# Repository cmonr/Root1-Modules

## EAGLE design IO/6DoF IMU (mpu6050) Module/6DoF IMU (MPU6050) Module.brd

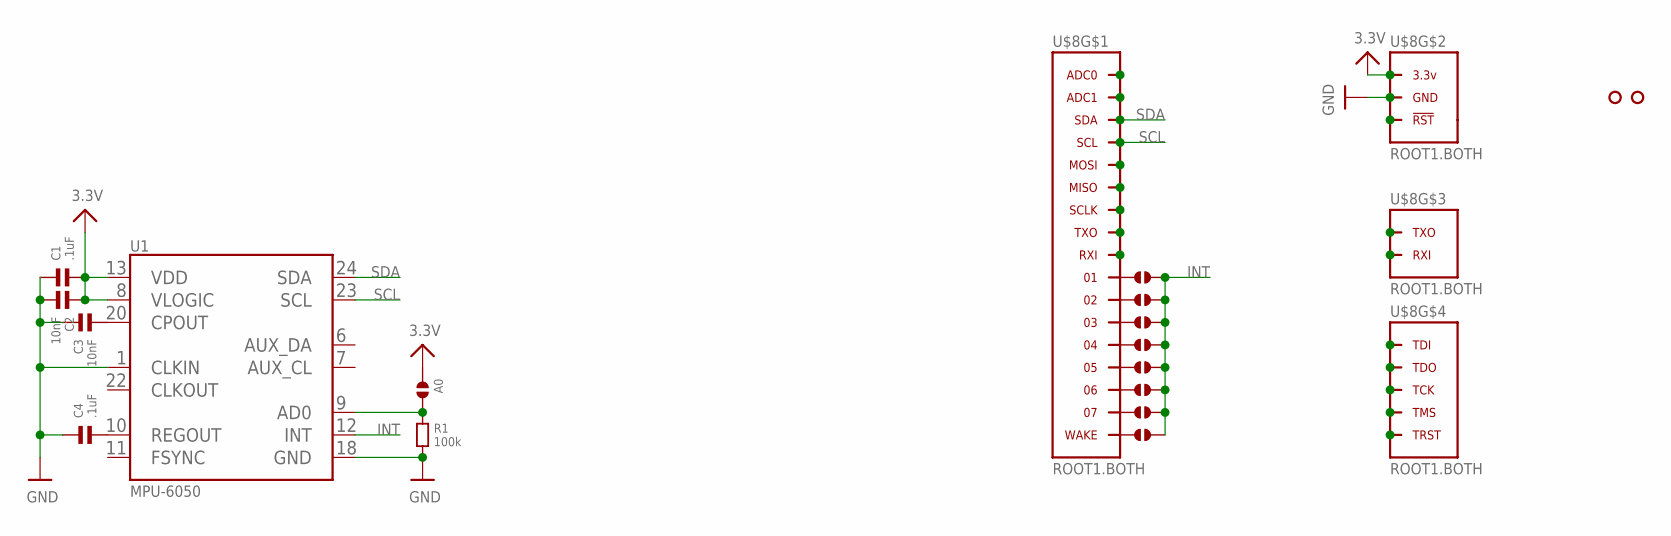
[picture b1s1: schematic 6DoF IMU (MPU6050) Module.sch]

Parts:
A0: SOLDERJUMPER.2.LRG; 2.LRG
C1, C4: .1uF; 0603
C2, C3: 10nF; 0603
J1, J2, J3, J4, J5, J6, J7, J8: SOLDERJUMPER.2.SML; 2.SML
R1: 100k; 0603
U1: MPU-6050; QFN
U$3, U$4: HOLE.2MM; 2MM
U$8: ROOT1.BOTH

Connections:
3.3V: A0.1, C1.2, C2.1, U1.8 (VLOGIC), U1.13 (VDD), U$8.3.3V@1 (3.3V), U$8.3.3V@2 (3.3V), U$8.3.3V@3 (3.3V), U$8.3.3V@4 (3.3V), U$8.3.3V@5 (3.3V), U$8.3.3V@6 (3.3V), U$8.3.3V@7 (3.3V), U$8.3.3V@8 (3.3V), U$8.3.3V@9 (3.3V), U$8.3.3V@10 (3.3V), U$8.3.3V@11 (3.3V), U$8.3.3V@12 (3.3V), U$8.3.3V@13 (3.3V), U$8.3.3V@14 (3.3V), U$8.3.3V@15 (3.3V), U$8.3.3V@16 (3.3V), U$8.3.3V@17 (3.3V), U$8.3.3V@18 (3.3V), U$8.3.3V@19 (3.3V), U$8.3.3V@20 (3.3V), U$8.3.3V@21 (3.3V), U$8.3.3V@22 (3.3V), U$8.3.3V@23 (3.3V), U$8.3.3V@24 (3.3V), U$8.3.3V@VIA (3.3V)
GND: C1.1, C2.2, C3.1, C4.1, R1.2, U1.1 (CLKIN), U1.18 (GND), U$8.GND@1 (GND), U$8.GND@2 (GND), U$8.GND@3 (GND), U$8.GND@4 (GND), U$8.GND@5 (GND), U$8.GND@6 (GND), U$8.GND@7 (GND), U$8.GND@8 (GND), U$8.GND@9 (GND), U$8.GND@10 (GND), U$8.GND@11 (GND), U$8.GND@12 (GND), U$8.GND@13 (GND), U$8.GND@14 (GND), U$8.GND@15 (GND), U$8.GND@16 (GND), U$8.GND@17 (GND), U$8.GND@18 (GND), U$8.GND@19 (GND), U$8.GND@20 (GND), U$8.GND@21 (GND), U$8.GND@22 (GND), U$8.GND@23 (GND), U$8.GND@24 (GND), U$8.GND@25 (GND), U$8.GND@26 (GND), U$8.GND@VIA (GND)
INT: J1.2, J2.2, J3.2, J4.2, J5.2, J6.2, J7.2, J8.2, U1.12 (INT)
unnamed: U$8.ADC0, U$8.ADC0@1 (ADC0), U$8.ADC0@VIA (ADC0)
unnamed: U$8.ADC1, U$8.ADC1@1 (ADC1), U$8.ADC1@VIA (ADC1)
unnamed: J1.1, U$8.01, U$8.01@1 (01), U$8.01@VIA (01)
unnamed: U$8.RST (!RST), U$8.RST@1 (!RST), U$8.RST@VIA (!RST)
unnamed: U$8.MOSI, U$8.MOSI@1 (MOSI), U$8.MOSI@VIA (MOSI)
unnamed: U$8.MISO, U$8.MISO@1 (MISO), U$8.MISO@VIA (MISO)
unnamed: U$8.SCLK, U$8.SCLK@1 (SCLK), U$8.SCLK@VIA (SCLK)
unnamed: U$8.TXO.DBG (TXO), U$8.TXO.DBG@1 (TXO), U$8.TXO.DBG@VIA (TXO)
unnamed: U$8.RXI.DBG (RXI), U$8.RXI.DBG@1 (RXI), U$8.RXI.DBG@VIA (RXI)
unnamed: U$8.TDI, U$8.TDI@1 (TDI), U$8.TDI@VIA (TDI)
unnamed: U$8.TDO, U$8.TDO@1 (TDO), U$8.TDO@VIA (TDO)
unnamed: U$8.TCK, U$8.TCK@1 (TCK), U$8.TCK@VIA (TCK)
unnamed: U$8.RXI, U$8.RXI@1 (RXI), U$8.RXI@VIA (RXI)
unnamed: U$8.TXO, U$8.TXO@1 (TXO), U$8.TXO@VIA (TXO)
unnamed: U$8.TMS, U$8.TMS@1 (TMS), U$8.TMS@VIA (TMS)
unnamed: C3.2, U1.20 (CPOUT)
unnamed: U$8.TRST, U$8.TRST@1 (TRST), U$8.TRST@VIA (TRST)
unnamed: A0.2, R1.1, U1.9 (AD0)
unnamed: J2.1, U$8.02, U$8.02@1 (02), U$8.02@VIA (02)
unnamed: C4.2, U1.10 (REGOUT)
unnamed: J3.1, U$8.03, U$8.03@1 (03), U$8.03@VIA (03)
unnamed: J4.1, U$8.04, U$8.04@1 (04), U$8.04@VIA (04)
unnamed: J5.1, U$8.05, U$8.05@1 (05), U$8.05@VIA (05)
unnamed: J6.1, U$8.06, U$8.06@1 (06), U$8.06@VIA (06)
unnamed: J7.1, U$8.07, U$8.07@1 (07), U$8.07@VIA (07)
unnamed: J8.1, U$8.WAKE, U$8.WAKE@1 (WAKE), U$8.WAKE@VIA (WAKE)
SCL: U1.23 (SCL), U$8.SCL, U$8.SCL@1 (SCL), U$8.SCL@VIA (SCL)
SDA: U1.24 (SDA), U$8.SDA, U$8.SDA@1 (SDA), U$8.SDA@VIA (SDA)

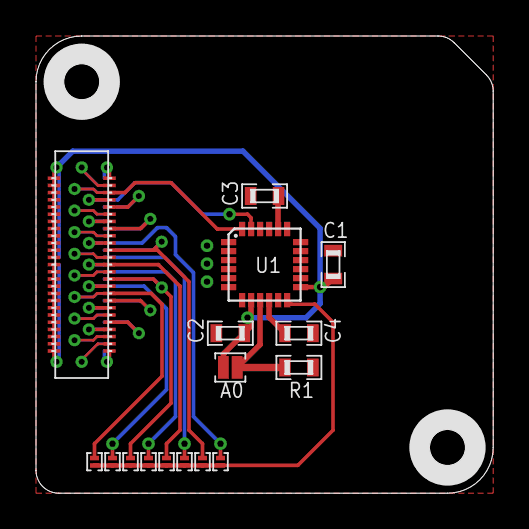
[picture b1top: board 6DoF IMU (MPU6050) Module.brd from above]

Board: 2 copper layers, 25.4 x 25.4 mm, 18 parts (0 on the bottom side), 31 nets.

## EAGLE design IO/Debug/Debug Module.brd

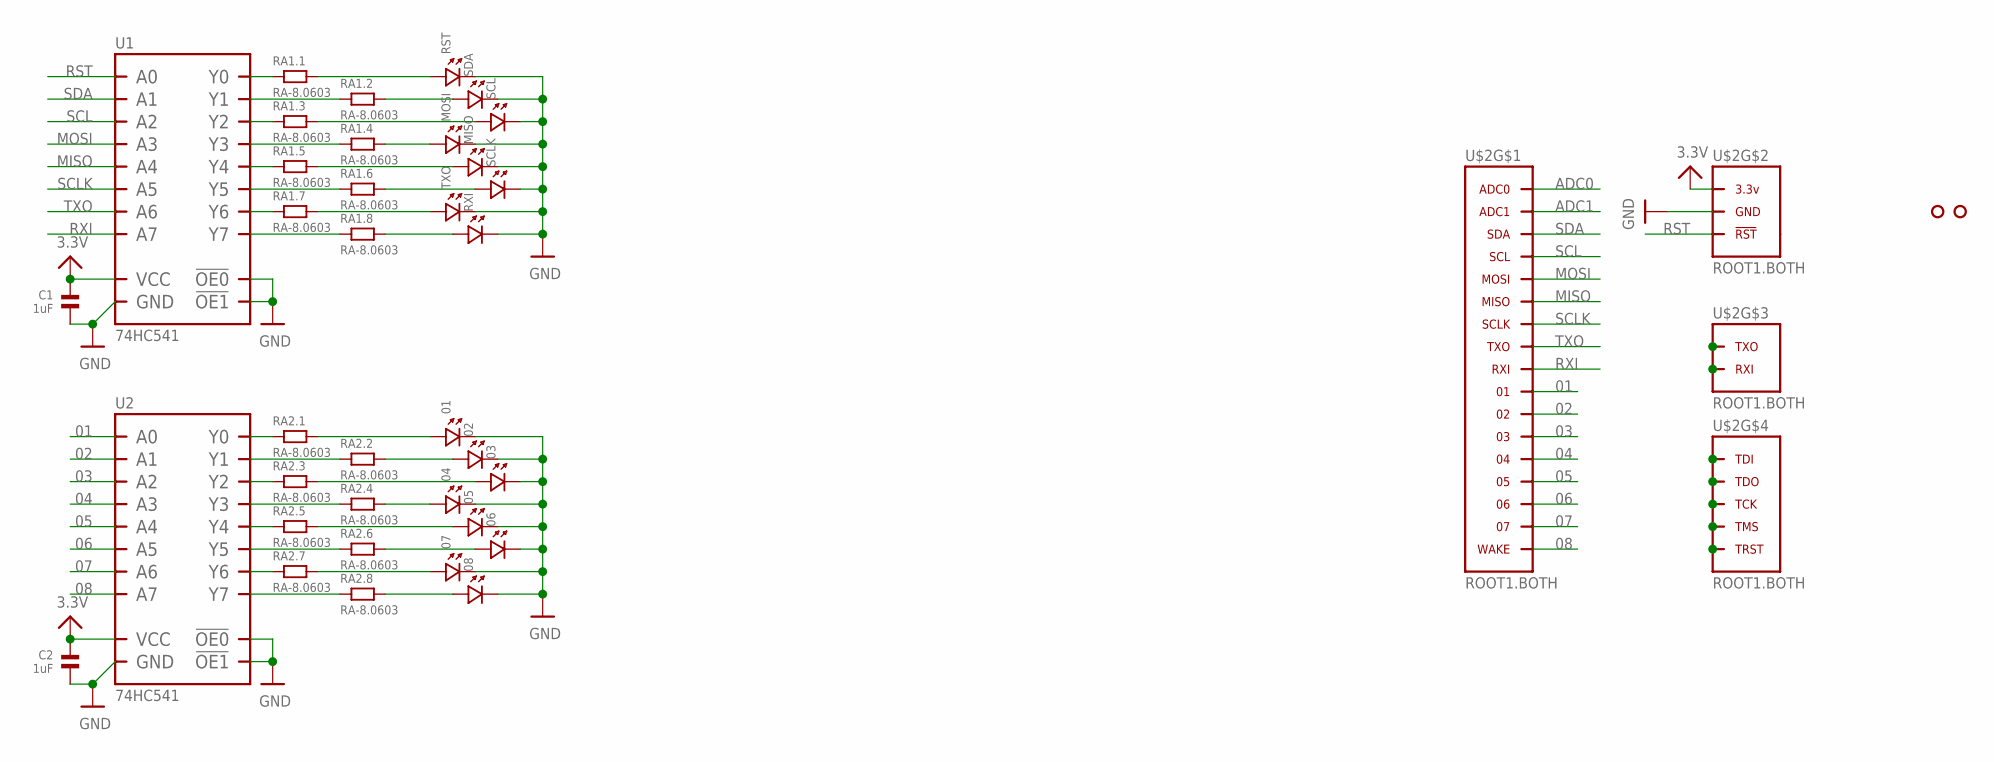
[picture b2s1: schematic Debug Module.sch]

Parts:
01, 02, 03, 04, 05, 06, 07, 08: LED.0603; 0603.LED
C1, C2: 1uF; 0603
MISO: LED.0603; 0603.LED
MOSI: LED.0603; 0603.LED
RA1, RA2: RA-8.0603; 0603.8.C
RST: LED.0603; 0603.LED
RXI: LED.0603; 0603.LED
SCL: LED.0603; 0603.LED
SCLK: LED.0603; 0603.LED
SDA: LED.0603; 0603.LED
TXO: LED.0603; 0603.LED
U1, U2: 74HC541; DHVQFN20
U$2: ROOT1.BOTH
U$3, U$4: HOLE.2MM; 2MM

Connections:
01: U2.2 (A0), U$2.01, U$2.01@1 (01), U$2.01@VIA (01)
02: U2.3 (A1), U$2.02, U$2.02@1 (02), U$2.02@VIA (02)
03: U2.4 (A2), U$2.03, U$2.03@1 (03), U$2.03@VIA (03)
3.3V: C1.1, C2.1, U1.20 (VCC), U2.20 (VCC), U$2.3.3V@1 (3.3V), U$2.3.3V@2 (3.3V), U$2.3.3V@3 (3.3V), U$2.3.3V@4 (3.3V), U$2.3.3V@5 (3.3V), U$2.3.3V@6 (3.3V), U$2.3.3V@7 (3.3V), U$2.3.3V@8 (3.3V), U$2.3.3V@9 (3.3V), U$2.3.3V@10 (3.3V), U$2.3.3V@11 (3.3V), U$2.3.3V@12 (3.3V), U$2.3.3V@13 (3.3V), U$2.3.3V@14 (3.3V), U$2.3.3V@15 (3.3V), U$2.3.3V@16 (3.3V), U$2.3.3V@17 (3.3V), U$2.3.3V@18 (3.3V), U$2.3.3V@19 (3.3V), U$2.3.3V@20 (3.3V), U$2.3.3V@21 (3.3V), U$2.3.3V@22 (3.3V), U$2.3.3V@23 (3.3V), U$2.3.3V@24 (3.3V), U$2.3.3V@VIA (3.3V)
04: U2.5 (A3), U$2.04, U$2.04@1 (04), U$2.04@VIA (04)
05: U2.6 (A4), U$2.05, U$2.05@1 (05), U$2.05@VIA (05)
06: U2.7 (A5), U$2.06, U$2.06@1 (06), U$2.06@VIA (06)
07: U2.8 (A6), U$2.07, U$2.07@1 (07), U$2.07@VIA (07)
08: U2.9 (A7), U$2.WAKE, U$2.WAKE@1 (WAKE), U$2.WAKE@VIA (WAKE)
ADC0: U$2.ADC0, U$2.ADC0@1 (ADC0), U$2.ADC0@VIA (ADC0)
ADC1: U$2.ADC1, U$2.ADC1@1 (ADC1), U$2.ADC1@VIA (ADC1)
GND: 01.P$2 (2), 02.P$2 (2), 03.P$2 (2), 04.P$2 (2), 05.P$2 (2), 06.P$2 (2), 07.P$2 (2), 08.P$2 (2), C1.2, C2.2, MISO.P$2 (2), MOSI.P$2 (2), RST.P$2 (2), RXI.P$2 (2), SCL.P$2 (2), SCLK.P$2 (2), SDA.P$2 (2), TXO.P$2 (2), U1.1 (!OE0!), U1.10 (GND), U1.19 (!OE1!), U1.PAD (GND), U2.1 (!OE0!), U2.10 (GND), U2.19 (!OE1!), U2.PAD (GND), U$2.GND@1 (GND), U$2.GND@2 (GND), U$2.GND@3 (GND), U$2.GND@4 (GND), U$2.GND@5 (GND), U$2.GND@6 (GND), U$2.GND@7 (GND), U$2.GND@8 (GND), U$2.GND@9 (GND), U$2.GND@10 (GND), U$2.GND@11 (GND), U$2.GND@12 (GND), U$2.GND@13 (GND), U$2.GND@14 (GND), U$2.GND@15 (GND), U$2.GND@16 (GND), U$2.GND@17 (GND), U$2.GND@18 (GND), U$2.GND@19 (GND), U$2.GND@20 (GND), U$2.GND@21 (GND), U$2.GND@22 (GND), U$2.GND@23 (GND), U$2.GND@24 (GND), U$2.GND@25 (GND), U$2.GND@26 (GND), U$2.GND@VIA (GND)
MISO: U1.6 (A4), U$2.MISO, U$2.MISO@1 (MISO), U$2.MISO@VIA (MISO)
MOSI: U1.5 (A3), U$2.MOSI, U$2.MOSI@1 (MOSI), U$2.MOSI@VIA (MOSI)
unnamed: U$2.TXO.DBG (TXO), U$2.TXO.DBG@1 (TXO), U$2.TXO.DBG@VIA (TXO)
unnamed: RA2.1, U2.18 (Y0)
unnamed: RA2.3 (1), U2.17 (Y1)
unnamed: RA2.5 (1), U2.16 (Y2)
unnamed: RA2.7 (1), U2.15 (Y3)
unnamed: RA2.9 (1), U2.14 (Y4)
unnamed: RA2.11 (1), U2.13 (Y5)
unnamed: RA2.13 (1), U2.12 (Y6)
unnamed: RA2.15 (1), U2.11 (Y7)
unnamed: 07.P$1 (1), RA2.14 (2)
unnamed: 08.P$1 (1), RA2.16 (2)
unnamed: 06.P$1 (1), RA2.12 (2)
unnamed: 05.P$1 (1), RA2.10 (2)
unnamed: 04.P$1 (1), RA2.8 (2)
unnamed: 03.P$1 (1), RA2.6 (2)
unnamed: 02.P$1 (1), RA2.4 (2)
unnamed: 01.P$1 (1), RA2.2
unnamed: U$2.RXI.DBG (RXI), U$2.RXI.DBG@1 (RXI), U$2.RXI.DBG@VIA (RXI)
unnamed: U$2.TDI, U$2.TDI@1 (TDI), U$2.TDI@VIA (TDI)
unnamed: U$2.TCK, U$2.TCK@1 (TCK), U$2.TCK@VIA (TCK)
unnamed: U$2.TDO, U$2.TDO@1 (TDO), U$2.TDO@VIA (TDO)
unnamed: U$2.TMS, U$2.TMS@1 (TMS), U$2.TMS@VIA (TMS)
unnamed: U$2.TRST, U$2.TRST@1 (TRST), U$2.TRST@VIA (TRST)
unnamed: RA1.1, U1.18 (Y0)
unnamed: RA1.3 (1), U1.17 (Y1)
unnamed: RA1.5 (1), U1.16 (Y2)
unnamed: RA1.7 (1), U1.15 (Y3)
unnamed: RA1.9 (1), U1.14 (Y4)
unnamed: RA1.11 (1), U1.13 (Y5)
unnamed: RA1.13 (1), U1.12 (Y6)
unnamed: RA1.15 (1), U1.11 (Y7)
unnamed: RA1.14 (2), TXO.P$1 (1)
unnamed: RA1.16 (2), RXI.P$1 (1)
unnamed: RA1.12 (2), SCLK.P$1 (1)
unnamed: MISO.P$1 (1), RA1.10 (2)
unnamed: MOSI.P$1 (1), RA1.8 (2)
unnamed: RA1.6 (2), SCL.P$1 (1)
unnamed: RA1.4 (2), SDA.P$1 (1)
unnamed: RA1.2, RST.P$1 (1)
RST: U1.2 (A0), U$2.RST (!RST), U$2.RST@1 (!RST), U$2.RST@VIA (!RST)
RXI: U1.9 (A7), U$2.RXI, U$2.RXI@1 (RXI), U$2.RXI@VIA (RXI)
SCL: U1.4 (A2), U$2.SCL, U$2.SCL@1 (SCL), U$2.SCL@VIA (SCL)
SCLK: U1.7 (A5), U$2.SCLK, U$2.SCLK@1 (SCLK), U$2.SCLK@VIA (SCLK)
SDA: U1.3 (A1), U$2.SDA, U$2.SDA@1 (SDA), U$2.SDA@VIA (SDA)
TXO: U1.8 (A6), U$2.TXO, U$2.TXO@1 (TXO), U$2.TXO@VIA (TXO)

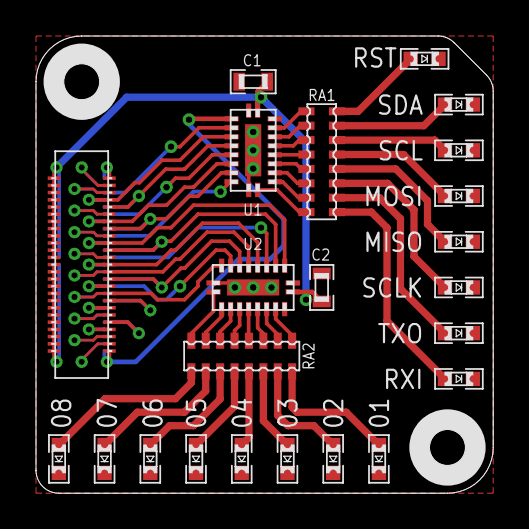
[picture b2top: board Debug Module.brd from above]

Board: 2 copper layers, 25.4 x 25.4 mm, 25 parts (0 on the bottom side), 59 nets.

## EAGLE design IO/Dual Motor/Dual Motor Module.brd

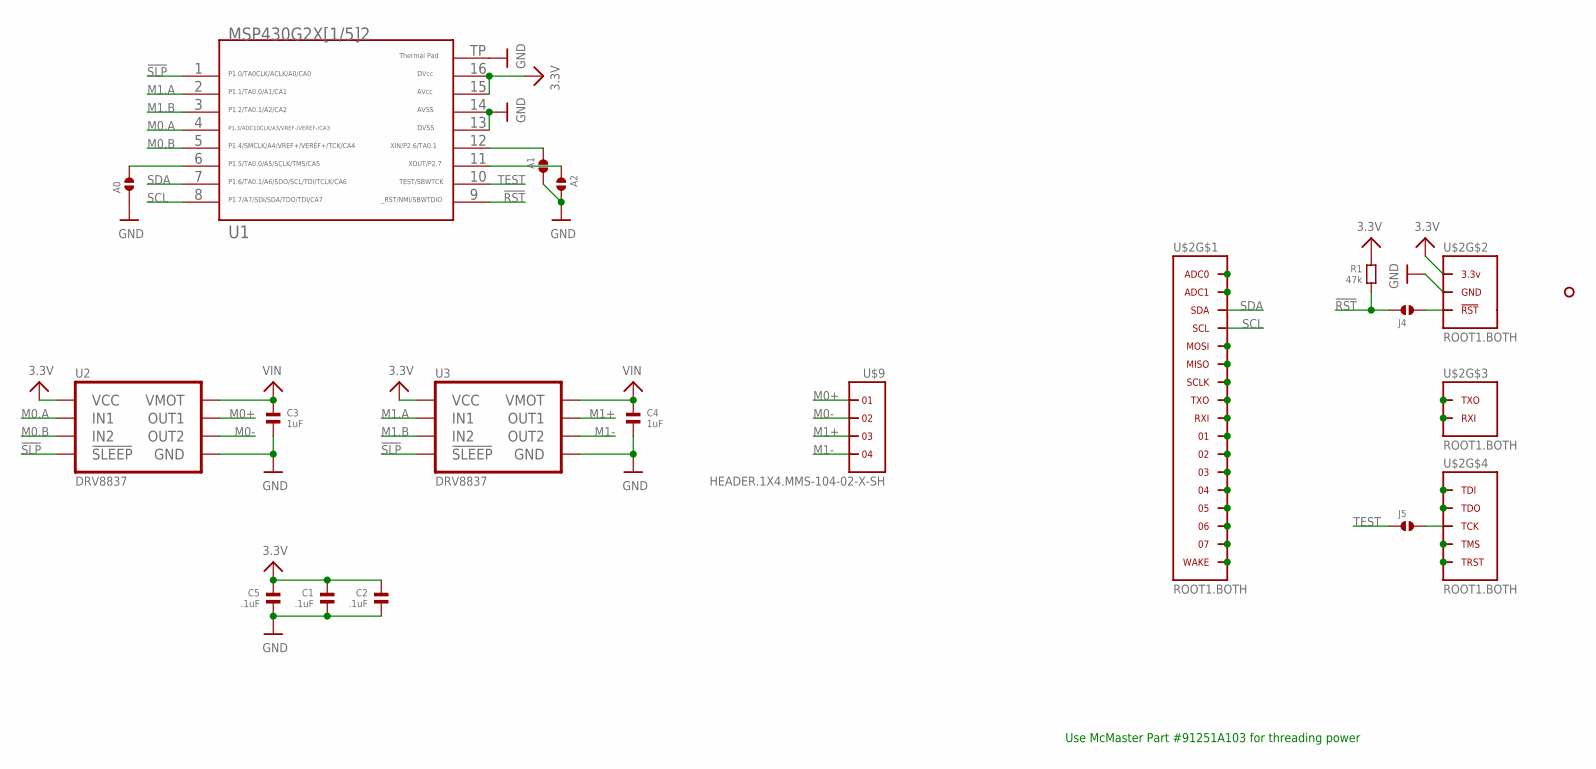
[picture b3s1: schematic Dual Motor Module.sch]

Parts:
A0, A1, A2: SOLDERJUMPER.2.MED; 2.MED
C1, C2, C5: .1uF; 0603
C3, C4: 1uF; 0603
J4, J5: SOLDERJUMPER.2.MED; 2.MED
R1: 47k; 0603
U1: MSP430G2452.QFN16; RSA16
U2, U3: DRV8837; DSG
U$2: ROOT1.BOTH
U$4: HOLE.#2; #2
U$9: HEADER.1X4.MMS-104-02-X-SH; MMS-104-02-X-SH

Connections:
3.3V: C1.1, C2.1, C5.1, R1.1, U1.15, U1.16, U2.8 (VCC), U3.8 (VCC), U$2.3.3V@1 (3.3V), U$2.3.3V@2 (3.3V), U$2.3.3V@3 (3.3V), U$2.3.3V@4 (3.3V), U$2.3.3V@5 (3.3V), U$2.3.3V@6 (3.3V), U$2.3.3V@7 (3.3V), U$2.3.3V@8 (3.3V), U$2.3.3V@9 (3.3V), U$2.3.3V@10 (3.3V), U$2.3.3V@11 (3.3V), U$2.3.3V@12 (3.3V), U$2.3.3V@13 (3.3V), U$2.3.3V@14 (3.3V), U$2.3.3V@15 (3.3V), U$2.3.3V@16 (3.3V), U$2.3.3V@17 (3.3V), U$2.3.3V@18 (3.3V), U$2.3.3V@19 (3.3V), U$2.3.3V@20 (3.3V), U$2.3.3V@21 (3.3V), U$2.3.3V@22 (3.3V), U$2.3.3V@23 (3.3V), U$2.3.3V@24 (3.3V), U$2.3.3V@VIA (3.3V)
!RST: J4.1, R1.2, U1.9
!SLP: U1.1, U2.7 (!SLEEP), U3.7 (!SLEEP)
GND: A0.1, A1.2, A2.2, C1.2, C2.2, C3.2, C4.2, C5.2, U1.13, U1.14, U1.TP, U2.4 (GND), U2.PAD (GND), U3.4 (GND), U3.PAD (GND), U$2.GND@1 (GND), U$2.GND@2 (GND), U$2.GND@3 (GND), U$2.GND@4 (GND), U$2.GND@5 (GND), U$2.GND@6 (GND), U$2.GND@7 (GND), U$2.GND@8 (GND), U$2.GND@9 (GND), U$2.GND@10 (GND), U$2.GND@11 (GND), U$2.GND@12 (GND), U$2.GND@13 (GND), U$2.GND@14 (GND), U$2.GND@15 (GND), U$2.GND@16 (GND), U$2.GND@17 (GND), U$2.GND@18 (GND), U$2.GND@19 (GND), U$2.GND@20 (GND), U$2.GND@21 (GND), U$2.GND@22 (GND), U$2.GND@23 (GND), U$2.GND@24 (GND), U$2.GND@25 (GND), U$2.GND@26 (GND), U$2.GND@VIA (GND)
M0+: U2.2 (OUT1), U$9.1, U$9.1@1 (1)
M0-: U2.3 (OUT2), U$9.2, U$9.2@1 (2)
M0.A: U1.4, U2.6 (IN1)
M0.B: U1.5, U2.5 (IN2)
M1+: U3.2 (OUT1), U$9.3, U$9.3@1 (3)
M1-: U3.3 (OUT2), U$9.4, U$9.4@1 (4)
M1.A: U1.2, U3.6 (IN1)
M1.B: U1.3, U3.5 (IN2)
unnamed: U$2.04, U$2.04@1 (04), U$2.04@VIA (04)
unnamed: U$2.ADC1, U$2.ADC1@1 (ADC1), U$2.ADC1@VIA (ADC1)
unnamed: A0.2, U1.6
unnamed: A2.1, U1.11
unnamed: U$2.03, U$2.03@1 (03), U$2.03@VIA (03)
unnamed: U$2.MISO, U$2.MISO@1 (MISO), U$2.MISO@VIA (MISO)
unnamed: U$2.SCLK, U$2.SCLK@1 (SCLK), U$2.SCLK@VIA (SCLK)
unnamed: U$2.TXO, U$2.TXO@1 (TXO), U$2.TXO@VIA (TXO)
unnamed: U$2.RXI, U$2.RXI@1 (RXI), U$2.RXI@VIA (RXI)
unnamed: U$2.01, U$2.01@1 (01), U$2.01@VIA (01)
unnamed: U$2.02, U$2.02@1 (02), U$2.02@VIA (02)
unnamed: U$2.MOSI, U$2.MOSI@1 (MOSI), U$2.MOSI@VIA (MOSI)
unnamed: U$2.ADC0, U$2.ADC0@1 (ADC0), U$2.ADC0@VIA (ADC0)
unnamed: U$2.05, U$2.05@1 (05), U$2.05@VIA (05)
unnamed: U$2.06, U$2.06@1 (06), U$2.06@VIA (06)
unnamed: U$2.07, U$2.07@1 (07), U$2.07@VIA (07)
unnamed: U$2.WAKE, U$2.WAKE@1 (WAKE), U$2.WAKE@VIA (WAKE)
unnamed: U$2.TDI, U$2.TDI@1 (TDI), U$2.TDI@VIA (TDI)
unnamed: U$2.TDO, U$2.TDO@1 (TDO), U$2.TDO@VIA (TDO)
unnamed: J5.2, U$2.TCK, U$2.TCK@1 (TCK), U$2.TCK@VIA (TCK)
unnamed: U$2.TMS, U$2.TMS@1 (TMS), U$2.TMS@VIA (TMS)
unnamed: U$2.TRST, U$2.TRST@1 (TRST), U$2.TRST@VIA (TRST)
unnamed: U$2.RXI.DBG (RXI), U$2.RXI.DBG@1 (RXI), U$2.RXI.DBG@VIA (RXI)
unnamed: U$2.TXO.DBG (TXO), U$2.TXO.DBG@1 (TXO), U$2.TXO.DBG@VIA (TXO)
unnamed: J4.2, U$2.RST (!RST), U$2.RST@1 (!RST), U$2.RST@VIA (!RST)
unnamed: A1.1, U1.12
SCL: U1.8, U$2.SCL, U$2.SCL@1 (SCL), U$2.SCL@VIA (SCL)
SDA: U1.7, U$2.SDA, U$2.SDA@1 (SDA), U$2.SDA@VIA (SDA)
TEST: J5.1, U1.10
VIN: C3.1, C4.1, U2.1 (VMOT), U3.1 (VMOT)

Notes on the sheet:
Use McMaster Part #91251A103 for threading power

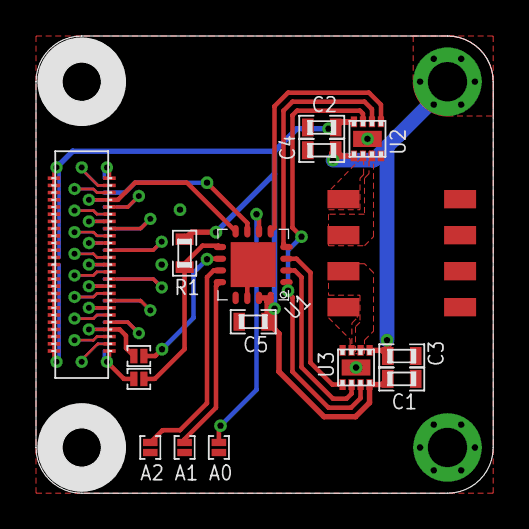
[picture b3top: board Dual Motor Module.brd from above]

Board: 2 copper layers, 25.4 x 25.4 mm, 18 parts (0 on the bottom side), 42 nets.

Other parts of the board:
U$3: HOLE.#2; #2

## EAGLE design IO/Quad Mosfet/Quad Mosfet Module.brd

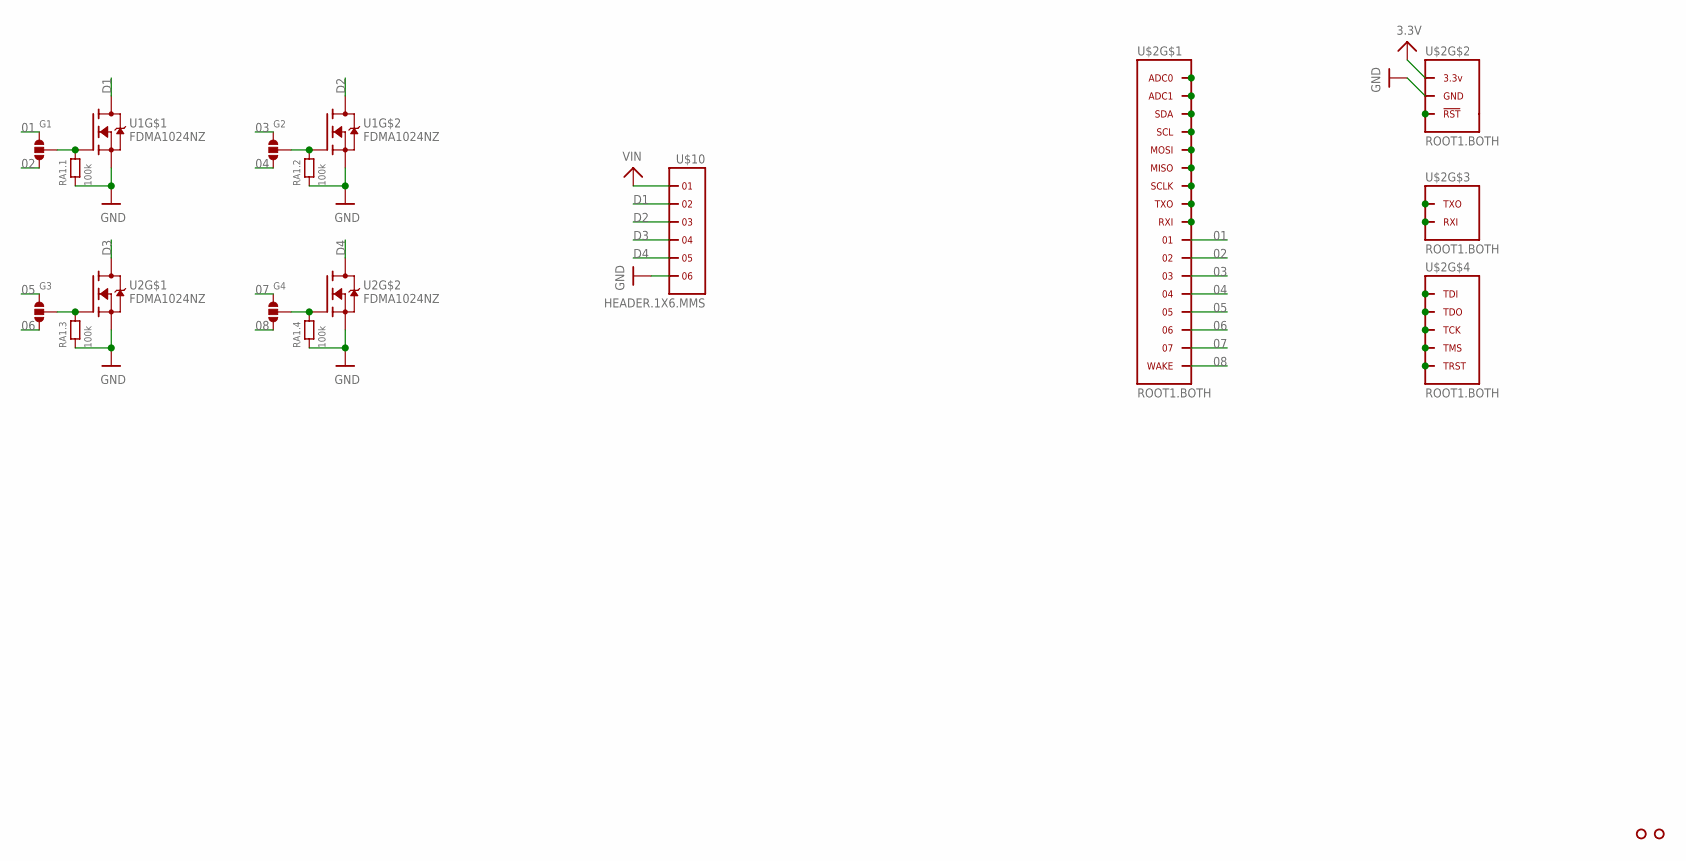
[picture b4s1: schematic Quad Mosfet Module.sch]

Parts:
G1, G2, G3, G4: SOLDERJUMPER.3.MED.12; 3.MED.12
RA1: 100k; 0603.4.C
U1, U2: FDMA1024NZ; MICROFET-6
U$2: ROOT1.BOTH
U$3, U$4: HOLE.#2; #2
U$10: HEADER.1X6.MMS; MMS-106-02-X-SH

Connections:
01: G1.1, U$2.01, U$2.01@1 (01), U$2.01@VIA (01)
02: G1.3, U$2.02, U$2.02@1 (02), U$2.02@VIA (02)
03: G2.1, U$2.03, U$2.03@1 (03), U$2.03@VIA (03)
3.3V: U$2.3.3V@1 (3.3V), U$2.3.3V@2 (3.3V), U$2.3.3V@3 (3.3V), U$2.3.3V@4 (3.3V), U$2.3.3V@5 (3.3V), U$2.3.3V@6 (3.3V), U$2.3.3V@7 (3.3V), U$2.3.3V@8 (3.3V), U$2.3.3V@9 (3.3V), U$2.3.3V@10 (3.3V), U$2.3.3V@11 (3.3V), U$2.3.3V@12 (3.3V), U$2.3.3V@13 (3.3V), U$2.3.3V@14 (3.3V), U$2.3.3V@15 (3.3V), U$2.3.3V@16 (3.3V), U$2.3.3V@17 (3.3V), U$2.3.3V@18 (3.3V), U$2.3.3V@19 (3.3V), U$2.3.3V@20 (3.3V), U$2.3.3V@21 (3.3V), U$2.3.3V@22 (3.3V), U$2.3.3V@23 (3.3V), U$2.3.3V@24 (3.3V), U$2.3.3V@VIA (3.3V)
04: G2.3, U$2.04, U$2.04@1 (04), U$2.04@VIA (04)
05: G3.1, U$2.05, U$2.05@1 (05), U$2.05@VIA (05)
06: G3.3, U$2.06, U$2.06@1 (06), U$2.06@VIA (06)
07: G4.1, U$2.07, U$2.07@1 (07), U$2.07@VIA (07)
08: G4.3, U$2.WAKE, U$2.WAKE@1 (WAKE), U$2.WAKE@VIA (WAKE)
D1: U1.D1 (D), U1.D1@PAD (D), U$10.2, U$10.2@1 (2)
D2: U1.D2 (D), U1.D2@PAD (D), U$10.3, U$10.3@1 (3)
D3: U2.D1 (D), U2.D1@PAD (D), U$10.4, U$10.4@1 (4)
D4: U2.D2 (D), U2.D2@PAD (D), U$10.5, U$10.5@1 (5)
GND: RA1.1, RA1.3 (1), RA1.5 (1), RA1.7 (1), U1.S1 (S), U1.S2 (S), U2.S1 (S), U2.S2 (S), U$2.GND@1 (GND), U$2.GND@2 (GND), U$2.GND@3 (GND), U$2.GND@4 (GND), U$2.GND@5 (GND), U$2.GND@6 (GND), U$2.GND@7 (GND), U$2.GND@8 (GND), U$2.GND@9 (GND), U$2.GND@10 (GND), U$2.GND@11 (GND), U$2.GND@12 (GND), U$2.GND@13 (GND), U$2.GND@14 (GND), U$2.GND@15 (GND), U$2.GND@16 (GND), U$2.GND@17 (GND), U$2.GND@18 (GND), U$2.GND@19 (GND), U$2.GND@20 (GND), U$2.GND@21 (GND), U$2.GND@22 (GND), U$2.GND@23 (GND), U$2.GND@24 (GND), U$2.GND@25 (GND), U$2.GND@26 (GND), U$2.GND@VIA (GND), U$10.6, U$10.6@1 (6)
unnamed: U$2.ADC1, U$2.ADC1@1 (ADC1), U$2.ADC1@VIA (ADC1)
unnamed: U$2.SDA, U$2.SDA@1 (SDA), U$2.SDA@VIA (SDA)
unnamed: U$2.SCL, U$2.SCL@1 (SCL), U$2.SCL@VIA (SCL)
unnamed: U$2.MISO, U$2.MISO@1 (MISO), U$2.MISO@VIA (MISO)
unnamed: U$2.SCLK, U$2.SCLK@1 (SCLK), U$2.SCLK@VIA (SCLK)
unnamed: U$2.TXO, U$2.TXO@1 (TXO), U$2.TXO@VIA (TXO)
unnamed: U$2.RXI, U$2.RXI@1 (RXI), U$2.RXI@VIA (RXI)
unnamed: U$2.MOSI, U$2.MOSI@1 (MOSI), U$2.MOSI@VIA (MOSI)
unnamed: U$2.ADC0, U$2.ADC0@1 (ADC0), U$2.ADC0@VIA (ADC0)
unnamed: U$2.TDI, U$2.TDI@1 (TDI), U$2.TDI@VIA (TDI)
unnamed: U$2.TDO, U$2.TDO@1 (TDO), U$2.TDO@VIA (TDO)
unnamed: U$2.RST (!RST), U$2.RST@1 (!RST), U$2.RST@VIA (!RST)
unnamed: U$2.TMS, U$2.TMS@1 (TMS), U$2.TMS@VIA (TMS)
unnamed: U$2.TRST, U$2.TRST@1 (TRST), U$2.TRST@VIA (TRST)
unnamed: U$2.RXI.DBG (RXI), U$2.RXI.DBG@1 (RXI), U$2.RXI.DBG@VIA (RXI)
unnamed: U$2.TXO.DBG (TXO), U$2.TXO.DBG@1 (TXO), U$2.TXO.DBG@VIA (TXO)
unnamed: U$2.TCK, U$2.TCK@1 (TCK), U$2.TCK@VIA (TCK)
unnamed: G1.2, RA1.2, U1.G1 (G)
unnamed: G2.2, RA1.4 (2), U1.G2 (G)
unnamed: G3.2, RA1.6 (2), U2.G1 (G)
unnamed: G4.2, RA1.8 (2), U2.G2 (G)
VIN: U$10.1, U$10.1@1 (1)

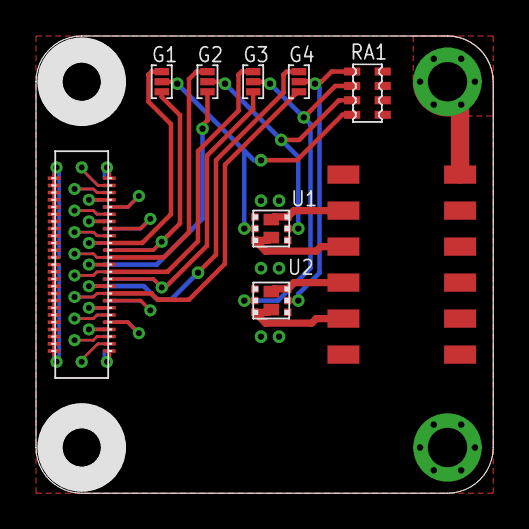
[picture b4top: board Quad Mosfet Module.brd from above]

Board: 2 copper layers, 25.4 x 25.4 mm, 11 parts (0 on the bottom side), 36 nets.

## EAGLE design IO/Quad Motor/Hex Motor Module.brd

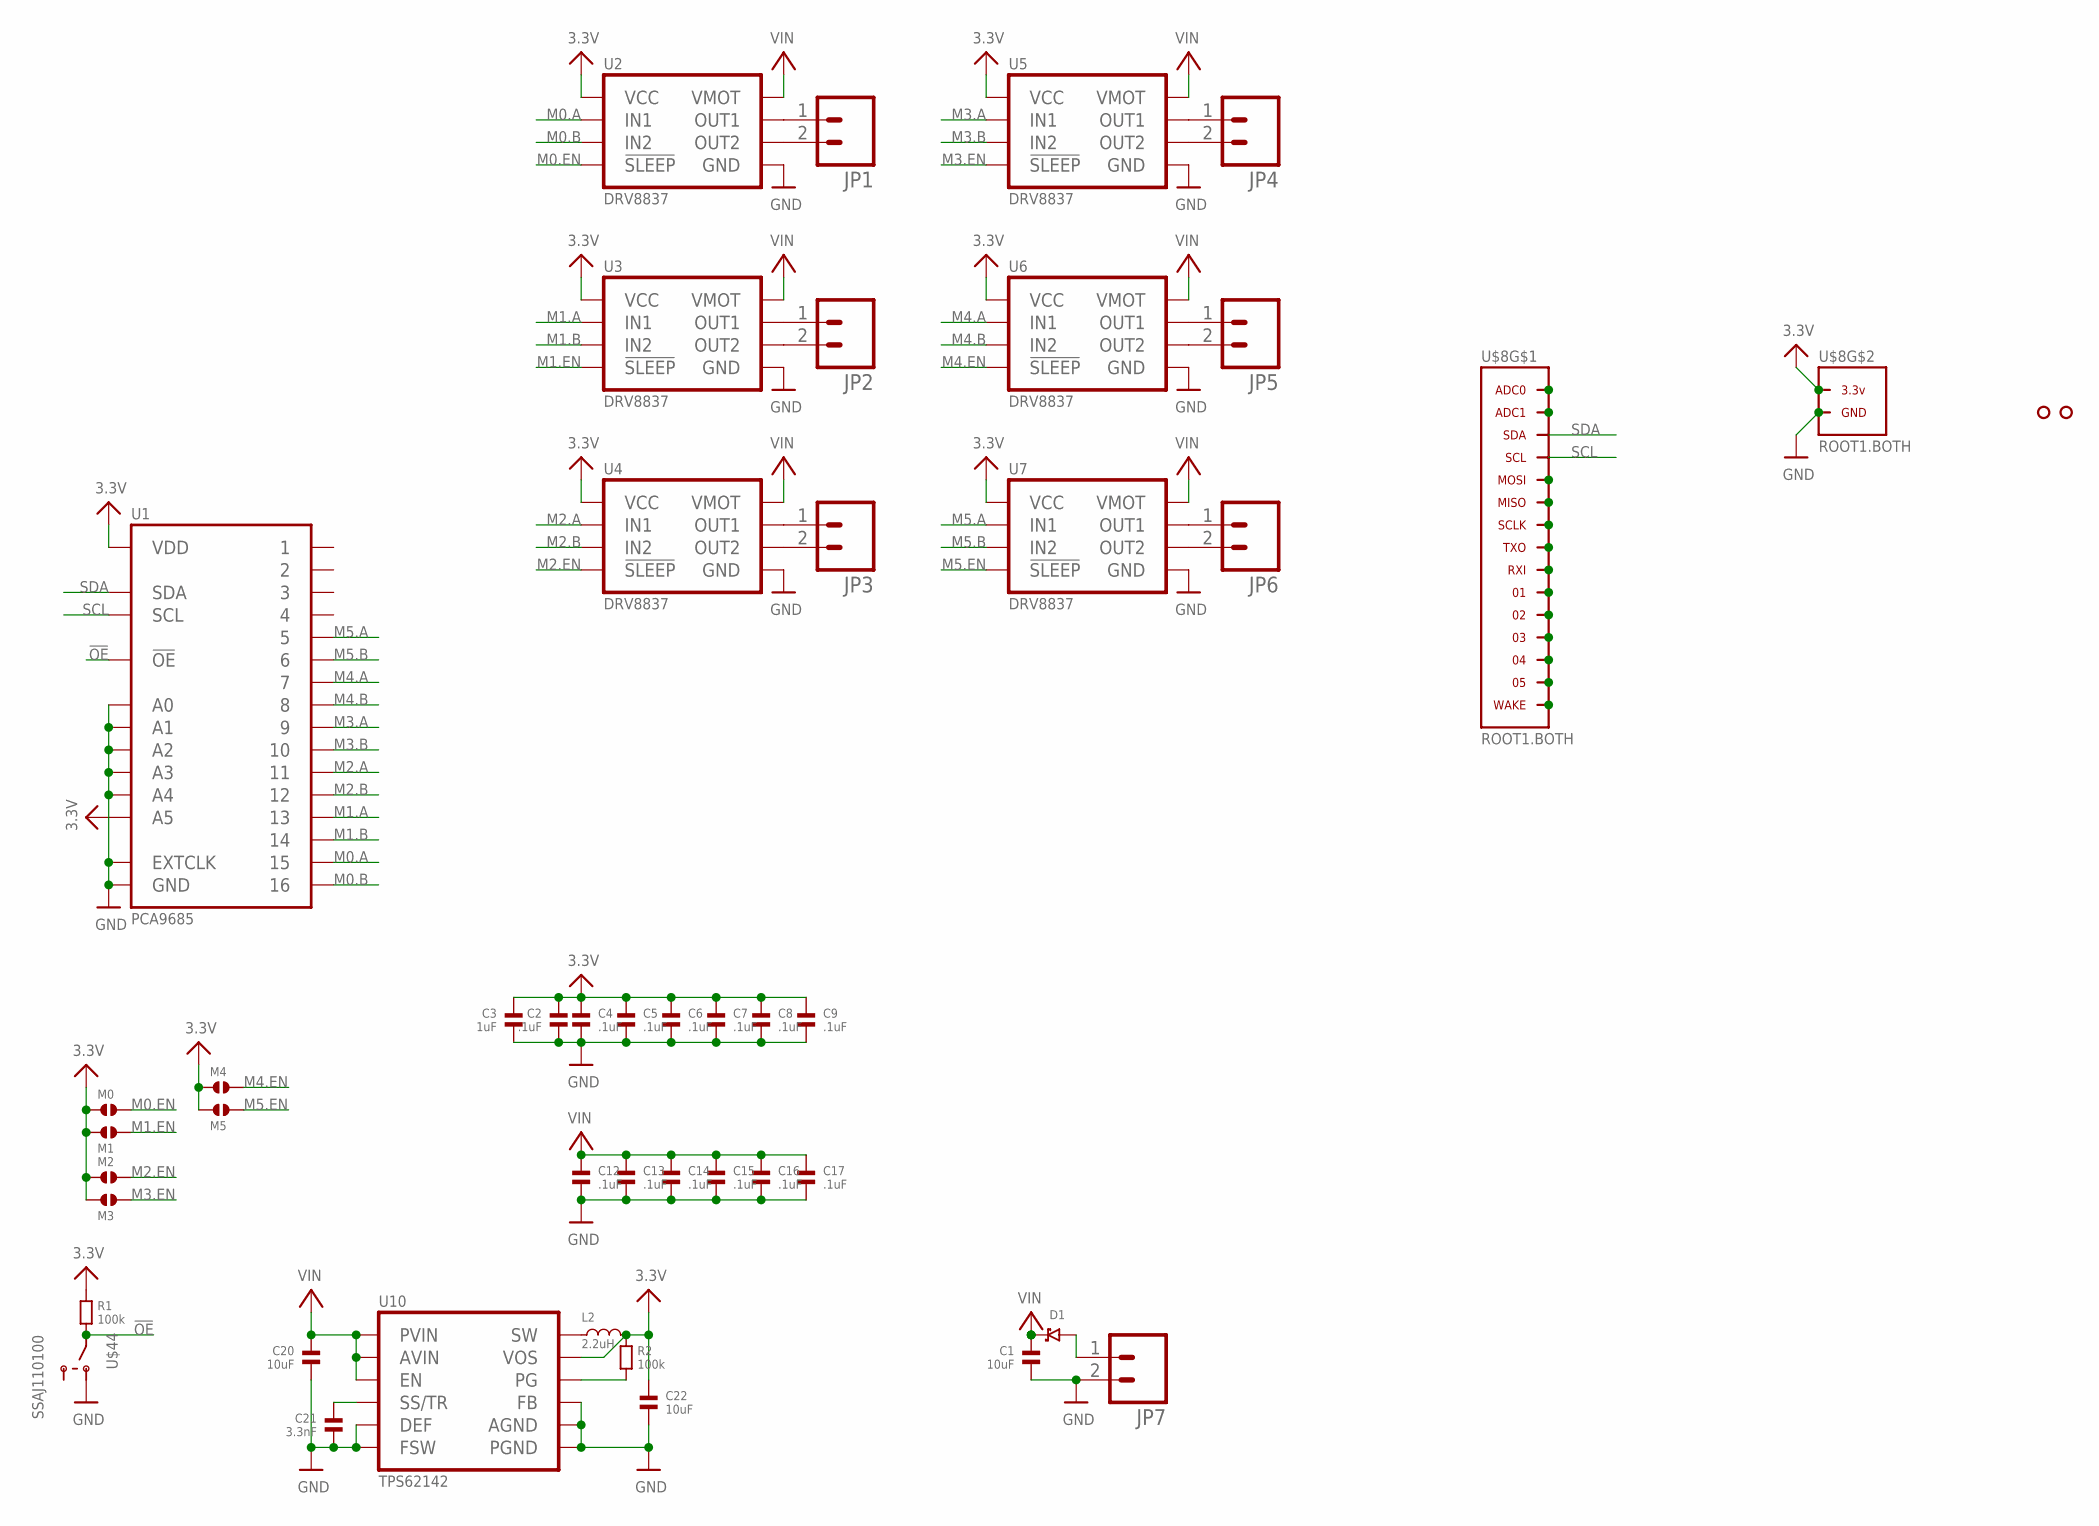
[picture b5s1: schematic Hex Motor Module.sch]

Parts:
C1: 10uF; 1206
C2: .1uF; 0603
C3: 1uF; 0603
C4, C5, C6, C7, C8, C9, C12, C13, C14, C15, C16, C17: .1uF; 0402
C20, C22: 10uF; 0805
C21: 3.3nF; 0603
D1: DIODE[SCHOTKY]-SOD123W; SOD123W
JP1, JP2, JP3, JP4, JP5, JP6, JP7: M023.5MM_LOCK; SCREWTERMINAL-3.5MM-2_LOCK
L2: 2.2uH; SRP4020
M0, M1, M2, M3, M4, M5: SOLDERJUMPER.2.LRG.PASTE; 2.LRG.PASTE
R1, R2: 100k; 0603
U1: PCA9685; HVQFN28
U2, U3, U4, U5, U6, U7: DRV8837; DSG
U10: TPS62142; RGT
U$3, U$4: HOLE.2MM; 2MM
U$8: ROOT1.BOTH
U$44: SSAJ110100

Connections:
3.3V: C2.1, C3.1, C4.1, C5.1, C6.1, C7.1, C8.1, C9.1, C22.1, L2.2, M0.1, M1.1, M2.1, M3.1, M4.1, M5.1, R1.1, R2.1, U1.24 (A5), U1.28 (VDD), U2.8 (VCC), U3.8 (VCC), U4.8 (VCC), U5.8 (VCC), U6.8 (VCC), U7.8 (VCC), U10.14 (VOS), U$8.3.3V@1 (3.3V), U$8.3.3V@2 (3.3V), U$8.3.3V@3 (3.3V), U$8.3.3V@4 (3.3V), U$8.3.3V@5 (3.3V), U$8.3.3V@6 (3.3V), U$8.3.3V@7 (3.3V), U$8.3.3V@8 (3.3V), U$8.3.3V@9 (3.3V), U$8.3.3V@10 (3.3V), U$8.3.3V@VIA (3.3V)
!OE: R1.2, U1.23 (!OE), U$44.C (1)
GND: C1.2, C2.2, C3.2, C4.2, C5.2, C6.2, C7.2, C8.2, C9.2, C12.2, C13.2, C14.2, C15.2, C16.2, C17.2, C20.2, C21.2, C22.2, JP7.2, U1.1 (A0), U1.2 (A1), U1.3 (A2), U1.4 (A3), U1.5 (A4), U1.14 (GND), U1.25 (EXTCLK), U1.PAD (GND), U2.4 (GND), U2.PAD (GND), U3.4 (GND), U3.PAD (GND), U4.4 (GND), U4.PAD (GND), U5.4 (GND), U5.PAD (GND), U6.4 (GND), U6.PAD (GND), U7.4 (GND), U7.PAD (GND), U10.5 (FB), U10.6 (AGND), U10.7 (FSW), U10.8 (DEF), U10.15 (PGND), U10.16 (PGND), U10.PAD (AGND), U$8.GND@1 (GND), U$8.GND@2 (GND), U$8.GND@3 (GND), U$8.GND@4 (GND), U$8.GND@5 (GND), U$8.GND@6 (GND), U$8.GND@7 (GND), U$8.GND@8 (GND), U$8.GND@9 (GND), U$8.GND@10 (GND), U$8.GND@11 (GND), U$8.GND@12 (GND), U$8.GND@13 (GND), U$8.GND@14 (GND), U$8.GND@15 (GND), U$8.GND@16 (GND), U$8.GND@17 (GND), U$8.GND@18 (GND), U$8.GND@19 (GND), U$8.GND@20 (GND), U$8.GND@VIA (GND), U$44.1 (2)
M0.A: U1.21 (15), U2.6 (IN1)
M0.B: U1.22 (16), U2.5 (IN2)
M0.EN: M0.2, U2.7 (!SLEEP)
M1.A: U1.19 (13), U3.6 (IN1)
M1.B: U1.20 (14), U3.5 (IN2)
M1.EN: M1.2, U3.7 (!SLEEP)
M2.A: U1.17 (11), U4.6 (IN1)
M2.B: U1.18 (12), U4.5 (IN2)
M2.EN: M2.2, U4.7 (!SLEEP)
M3.A: U1.15 (9), U5.6 (IN1)
M3.B: U1.16 (10), U5.5 (IN2)
M3.EN: M3.2, U5.7 (!SLEEP)
M4.A: U1.12 (7), U6.6 (IN1)
M4.B: U1.13 (8), U6.5 (IN2)
M4.EN: M4.2, U6.7 (!SLEEP)
M5.A: U1.10 (5), U7.6 (IN1)
M5.B: U1.11 (6), U7.5 (IN2)
M5.EN: M5.2, U7.7 (!SLEEP)
unnamed: U$8.ADC0, U$8.ADC0@1 (ADC0), U$8.ADC0@VIA (ADC0)
unnamed: U$8.ADC1, U$8.ADC1@1 (ADC1), U$8.ADC1@VIA (ADC1)
unnamed: L2.1, U10.1 (SW), U10.2 (SW), U10.3 (SW)
unnamed: R2.2, U10.4 (PG)
unnamed: U$8.MOSI, U$8.MOSI@1 (MOSI), U$8.MOSI@VIA (MOSI)
unnamed: U$8.MISO, U$8.MISO@1 (MISO), U$8.MISO@VIA (MISO)
unnamed: U$8.SCLK, U$8.SCLK@1 (SCLK), U$8.SCLK@VIA (SCLK)
unnamed: U$8.01 (TXO), U$8.01@1 (TXO), U$8.01@VIA (TXO)
unnamed: U$8.02 (RXI), U$8.02@1 (RXI), U$8.02@VIA (RXI)
unnamed: U$8.03 (01), U$8.03@1 (01), U$8.03@VIA (01)
unnamed: U$8.04 (02), U$8.04@1 (02), U$8.04@VIA (02)
unnamed: U$8.05 (03), U$8.05@1 (03), U$8.05@VIA (03)
unnamed: U$8.06 (04), U$8.06@1 (04), U$8.06@VIA (04)
unnamed: U$8.07 (05), U$8.07@1 (05), U$8.07@VIA (05)
unnamed: U$8.WAKE, U$8.WAKE@1 (WAKE), U$8.WAKE@VIA (WAKE)
unnamed: JP1.1, U2.2 (OUT1)
unnamed: JP1.2, U2.3 (OUT2)
unnamed: JP4.1, U5.2 (OUT1)
unnamed: JP4.2, U5.3 (OUT2)
unnamed: JP5.1, U6.2 (OUT1)
unnamed: JP5.2, U6.3 (OUT2)
unnamed: JP6.1, U7.2 (OUT1)
unnamed: JP6.2, U7.3 (OUT2)
unnamed: JP3.1, U4.2 (OUT1)
unnamed: JP3.2, U4.3 (OUT2)
unnamed: JP2.1, U3.2 (OUT1)
unnamed: JP2.2, U3.3 (OUT2)
unnamed: D1.P$1 (1), JP7.1
unnamed: C21.1, U10.9 (SS/TR)
SCL: U1.26 (SCL), U$8.SCL, U$8.SCL@1 (SCL), U$8.SCL@VIA (SCL)
SDA: U1.27 (SDA), U$8.SDA, U$8.SDA@1 (SDA), U$8.SDA@VIA (SDA)
VIN: C1.1, C12.1, C13.1, C14.1, C15.1, C16.1, C17.1, C20.1, D1.P$2 (2), U2.1 (VMOT), U3.1 (VMOT), U4.1 (VMOT), U5.1 (VMOT), U6.1 (VMOT), U7.1 (VMOT), U10.10 (AVIN), U10.11 (PVIN), U10.12 (PVIN), U10.13 (EN)

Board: 2 copper layers, 47 parts (7 on the bottom side), 53 nets, no tracks yet.

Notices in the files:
parts and their libraries:
SparkFun: Licensing: CC v3.0 Share-Alike You are welcome to use this library for commercial purposes.
